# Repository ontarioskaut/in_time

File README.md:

# Hardwarové věci k etapě InTime 2025
Tento repozitář vznikl pro uchování hardwarových věcí potřebných k táborové etapě skautského oddílu Ontario - InTime 2025. Tvoří jeden celek se softwarovým řešením systému pro uchovávání časů, uživatelů a tagů, který neleznete zde: https://github.com/ontarioskaut/tabor2025. Detailnější informace jsou k mání na naši skautské wiki: https://wiki.zlin6.cz/cs/technika/intime2025.

## Obecná probematika
Pro celotáborovou hru jsme se rozhodli udělat systém, vekterém dominuje odpočítávaný čas jako měna. Členi mají RFID náramky a v dílčích částech tábora mají možnost dostat kulaté RFID tagy jakožto coiny s nějakou hodnotou. Mají jak zisky, tak výdaje za různé věci a snaží se s tím hospodařit. Aby to fungovalo, použili jsme moderní technologie a naprogramovali časový server, který řeší management uživatelů, náramků, coinů. Prostě nadstavba s API a GUI nad databází.

Tento server běží na mikropočítači (zde použit ROCK PI S s druhou WiFi kartou) a vše komunikuje bezdrátově přes WiFi. Vedoucí mají možnost zasahovat do systému skrze webové prostředí nebo webovou aplikaci používající přímo NFC API v prohlížeči, členi mohou managovat svůj čas skrze time terminals (ty umožňují platit, převádět, skenovat coiny a zjišťovat zůstatek). Terminály mají uvnitř RFID čtečku a ESP32, přes které se hardware řídí a je prováděna komunikace s časovým serverem skrze REST API. 

Další částí jsou displeje pro zobrazování aktuálních časů hráčů. K tomu jsme vybrali vyřazené Buse 210 displeje z autobusů, protože jsou velké, vypadají cool a jsou oproti LED variantám velice energeticky úsporné. Tam byl problém se zobrazováním vlastních dat, protože se pro komunikaci používá sběrnice IBIS (sériová sběrnice posazená na 24V s pomalým baudratem) s uzavřeným komunikačním protokolem. Prostě technologie někdy z 80. let. Vzhledem k tomu, že se v původních verzích panelů ani nepočítalo s vlastní grafikou, která bude často updatovaná (v panelech je databáze předpřipravených obrazovek, pomocí příkazů se přepínají). Vznikla tedy potřeba vlastního řízení. Zde nám usnadnil práci člově, který stojí za Flipity 210: https://github.com/mcer12/Flippity210. Pro naše účely stačilo naprogramovat ESP01S modulek s firmwarem, který periodicky stahuje předpřipravené obrazovky z time serveru a posílá je k zobrazení.

## displays/display_tool
- GTK aplikace sloužící k roční přípravě a testování zobrazení na Buse210 displejích. Aplikace generuje base64-encoded string, který obsahuje obrazové a adresní informace a slouží k ovládání řídící desky u displejů. 
- Existují dvě modifikace:
  - display_tool.py - tato sloužila k sériovému ovládání displejů. I2C sběrnice s displejů 
  - display_tool_web.py - modifikace, která plive data kompatibilní s webovou verzí editoru. Autorovi se totiž líp pracuje v desktopové verzi a navíc má lepší řešení low_resolution vykreslování fontů.
  
## time_terminal
- Veškeré podklady k hardwaru time_terminalu vytvořené v KiCadu. Jsou tam vytvořené přímo manifacturing data, ale ty silně nedoporučuji používat, protože design desky obsahuje mnoho chyb, které bylo potřeba manuálně předrátovat. Jedná se hlavně o špatné použití pinů, které jsou připojeny k interní flashce, takže to způsobovalo problémy u programování. Potom jsou někte použity input only piny pro output a tak dále. Bohužel si autor při kreslení schémat nedostatečně přečetl dokumentaci ESP32 modulu a pak se divil.

## firmware/esp8266_buse_cient
- Firmware pro esp01S připojené do Flipity 210 desky u displeje. Tato verze se používá ve finálním stavu systému - prostě vše se renderuje na serveru a esp jenom periodicky posílá requesty a stahuje base64-encoded obrázky, které jen vyplivne na displej.
- Pro správní fungování na největší (čelní) variantě displeje s 5 flip-dot panely byl ve Flipity210 firmwaru pozměněn limit panelů a nastavený jinší count v sekci čtení konfiguračních jumperů.
- Nevím, jak je to ve vyšší verzi Flipity210 hardwaru, ale ve verzi 2.1 je potřeba dávat pozor na voltage spiky způsobené čínským step-down modulem. Na tomto jsem při testování spálil pár STM32 procesorů. Já to řešil pomocí přidání velkého kondenzátoru a TVS na výstup. 

## firmware/ostatní
- Předchzí iterace způsobené nedostatkem espéček v mém sklepě. Jednalo se o aloučení I2C a společné řízení a potom na delší vzdálenosti použití sériového protokolu, pomocí kterého se dalo řešit posílání přímo z počítače s převodníkem.

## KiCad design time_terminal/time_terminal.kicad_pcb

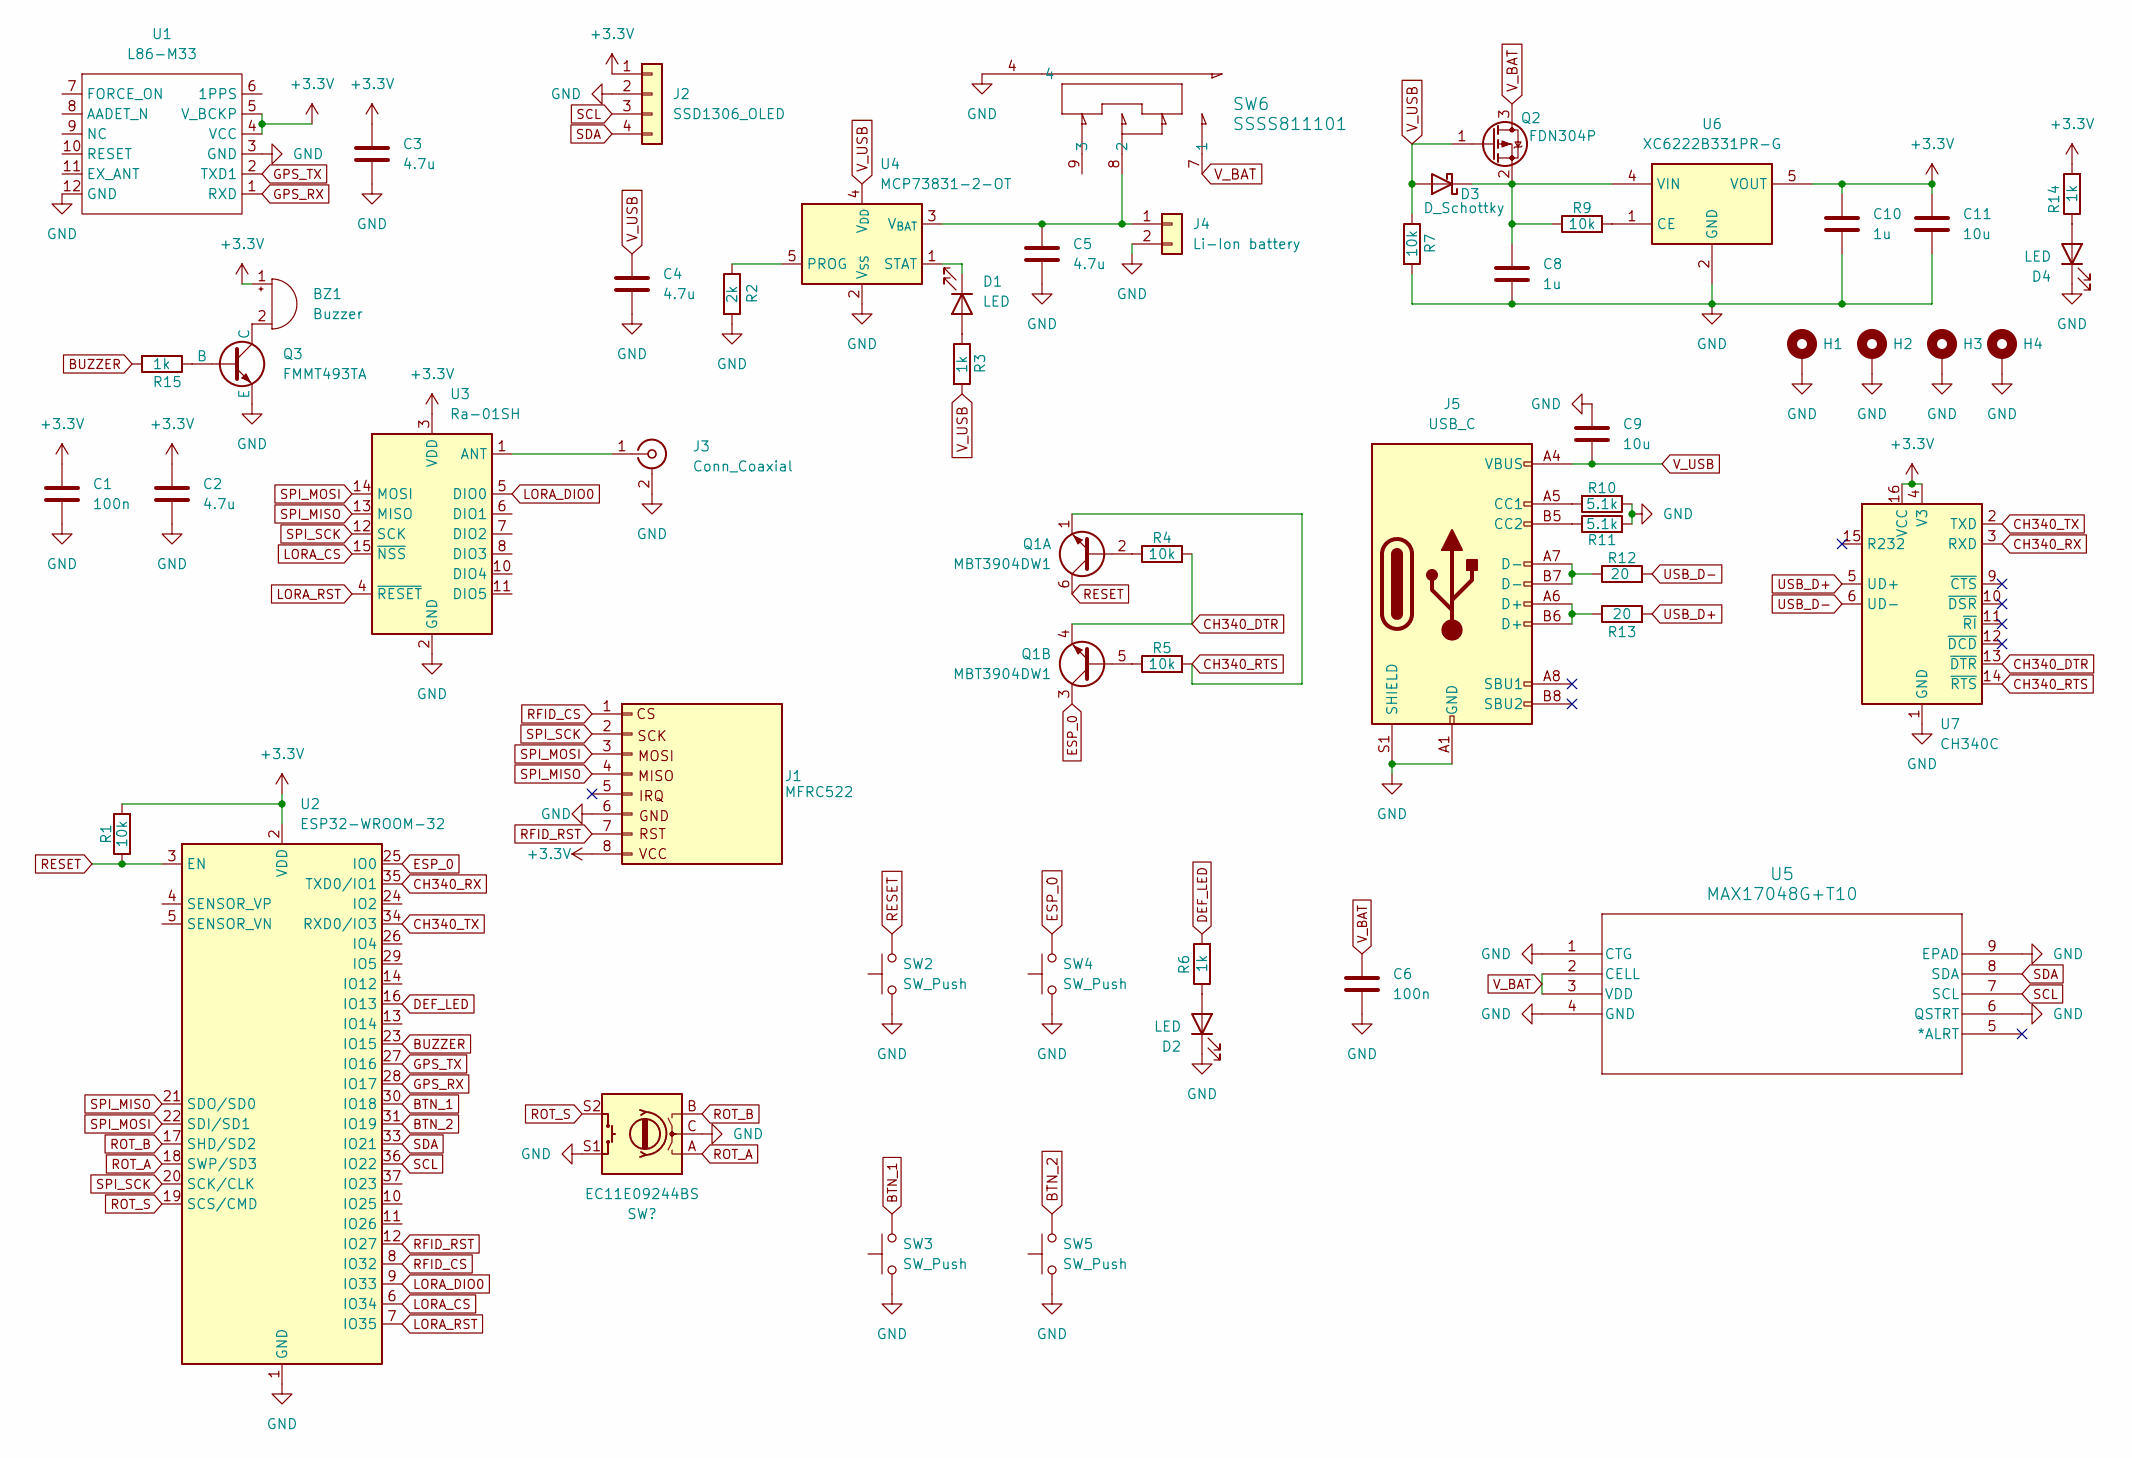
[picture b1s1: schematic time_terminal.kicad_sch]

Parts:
BZ1: Buzzer; Buzzer_TDK_PS1240P02BT_D12.2mm_H6.5mm; LCSC C360607
C1, C6: 100n; C_0603_1608Metric; LCSC C5137636
C2, C3, C4, C5: 4.7u; C_0603_1608Metric; LCSC C1705
C8, C10: 1u; C_0603_1608Metric; LCSC C1592
C9, C11: 10u; C_0603_1608Metric; LCSC C1691
D1, D2, D4: LED; LED_0603_1608Metric; LCSC C2286
D3: D_Schottky; D_SOD-123F; LCSC C223608
H1, H2, H3, H4: MountingHole_Pad; MountingHole_2.2mm_M2_Pad_Via
J1: MFRC522; PinHeader_1x08_P2.54mm_Vertical
J2: SSD1306_OLED; 128x64OLED
J3: Conn_Coaxial; SMA_Amphenol_132134-16_Vertical
J4: Li-Ion battery; BatteryHolder_Keystone_1042_1x18650
J5: USB_C; USB_C_Receptacle_HCTL_HC-TYPE-C-16P-01A; LCSC C2894897
Q1: MBT3904DW1; SOT-363_SC-70-6; LCSC C110150
Q2: FDN304P; SOT-23; LCSC C19188375
Q3: FMMT493TA; SOT-23-3; LCSC C435889
R1, R4, R5, R7, R9: 10k; R_0603_1608Metric_Pad0.98x0.95mm_HandSolder; LCSC C15401
R2: 2k; R_0603_1608Metric_Pad0.98x0.95mm_HandSolder; LCSC C25590
R3, R6, R14, R15: 1k; R_0603_1608Metric_Pad0.98x0.95mm_HandSolder; LCSC C22548
R10, R11: 5.1k; R_0603_1608Metric_Pad0.98x0.95mm_HandSolder; LCSC C2907114
R12, R13: 20; R_0603_1608Metric_Pad0.98x0.95mm_HandSolder; LCSC C25218
SW2, SW3, SW4, SW5: SW_Push; SW_Push_1P1T_XKB_TS-1187A; LCSC C318884
SW6: SSSS811101; SW4_SSSS811101_ALPS; LCSC C109335
U1: L86-M33
U2: ESP32-WROOM-32
U3: Ra-01SH; Ai-Thinker-Ra-01-LoRa
U4: MCP73831-2-OT; SOT-23-5; LCSC C424093
U5: MAX17048G+T10; 21-0168E_T822-3_MXM; LCSC C2682616
U6: XC6222B331PR-G; SOT-89-5; LCSC C3747687
U7: CH340C; SOIC-16_3.9x9.9mm_P1.27mm; LCSC C84681

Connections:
+3.3V: BZ1.1 (+), C1.1, C2.1, C3.1, C10.1, C11.1, J1.8, J2.1, R1.2, R14.2, U1.4 (VCC), U1.5 (V_BCKP), U2.2 (VDD), U3.3 (VDD), U6.5 (VOUT), U7.4 (V3), U7.16 (VCC)
BTN_1: SW3.2, U2.30 (IO18)
BTN_2: SW5.2, U2.31 (IO19)
BUZZER: R15.2, U2.23 (IO15)
CH340_DTR: Q1.4 (E2), R4.2, U7.13 (~DTR)
CH340_RTS: Q1.1 (E1), R5.2, U7.14 (~RTS)
CH340_RX: U2.35 (TXD0/IO1), U7.3 (RXD)
CH340_TX: U2.34 (RXD0/IO3), U7.2 (TXD)
DEF_LED: R6.2, U2.16 (IO13)
ESP_0: Q1.3 (C2), SW4.2, U2.25 (IO0)
GND: C1.2, C2.2, C3.2, C4.2, C5.2, C6.2, C8.2, C9.1, C10.2, C11.2, D2.1 (K), D4.1 (K), H1.1, H2.1, H3.1, H4.1, J1.6, J2.2, J3.2 (Ext), J4.2, J5.A1 (GND), J5.A12 (GND), J5.B1 (GND), J5.B12 (GND), J5.S1 (SHIELD), Q3.2 (E), R2.2, R7.2, R10.1, R11.2, SW2.1, SW3.1, SW4.1, SW5.1, SW6.4, U1.3 (GND), U1.12 (GND), U2.1 (GND), U2.15 (GND), U2.38 (GND), U2.39 (GND), U3.2 (GND), U3.9 (GND), U3.16 (GND), U4.2 (V_{SS}), U5.1 (CTG), U5.4 (GND), U5.6 (QSTRT), U5.9 (EPAD), U6.2 (GND), U7.1 (GND); also elsewhere on the board
GPS_RX: U1.1 (RXD), U2.28 (IO17)
GPS_TX: U1.2 (TXD1), U2.27 (IO16)
LORA_CS: U2.6 (IO34), U3.15 (~NSS)
LORA_DIO0: U2.9 (IO33), U3.5 (DIO0)
LORA_RST: U2.7 (IO35), U3.4 (~RESET)
unnamed: BZ1.2 (-), Q3.3 (C)
unnamed: D1.2 (A), R3.1
unnamed: D1.1 (K), U4.1 (STAT)
unnamed: D2.2 (A), R6.1
unnamed: C8.1, D3.1 (K), Q2.2 (S), R9.1, U6.4 (VIN)
unnamed: D4.2 (A), R14.1
unnamed: J3.1 (In), U3.1 (ANT)
unnamed: C5.1, J4.1, SW6.8 (2), U4.3 (V_{BAT})
unnamed: J5.A5 (CC1), R10.2
unnamed: J5.B5 (CC2), R11.1
unnamed: J5.A6 (D+), J5.B6 (D+), R13.1
unnamed: J5.A7 (D-), J5.B7 (D-), R12.1
unnamed: Q1.2 (B1), R4.1
unnamed: Q1.5 (B2), R5.1
unnamed: Q3.1 (B), R15.1
unnamed: R2.1, U4.5 (PROG)
unnamed: R9.2, U6.1 (CE)
RESET: Q1.6 (C1), R1.1, SW2.2, U2.3 (EN)
RFID_CS: J1.1, U2.8 (IO32)
RFID_RST: J1.7, U2.12 (IO27)
ROT_A: U2.18 (SWP/SD3); also elsewhere on the board
ROT_B: U2.17 (SHD/SD2); also elsewhere on the board
ROT_S: U2.19 (SCS/CMD); also elsewhere on the board
SCL: J2.3, U2.36 (IO22), U5.7 (SCL)
SDA: J2.4, U2.33 (IO21), U5.8 (SDA)
SPI_MISO: J1.4, U2.21 (SDO/SD0), U3.13 (MISO)
SPI_MOSI: J1.3, U2.22 (SDI/SD1), U3.14 (MOSI)
SPI_SCK: J1.2, U2.20 (SCK/CLK), U3.12 (SCK)
USB_D+: R13.2, U7.5 (UD+)
USB_D-: R12.2, U7.6 (UD-)
V_BAT: C6.1, Q2.3 (D), SW6.7 (1), U5.2 (CELL), U5.3 (VDD)
V_USB: C4.1, C9.2, D3.2 (A), J5.A4 (VBUS), J5.A9 (VBUS), J5.B4 (VBUS), J5.B9 (VBUS), Q2.1 (G), R3.2, R7.1, U4.4 (V_{DD})

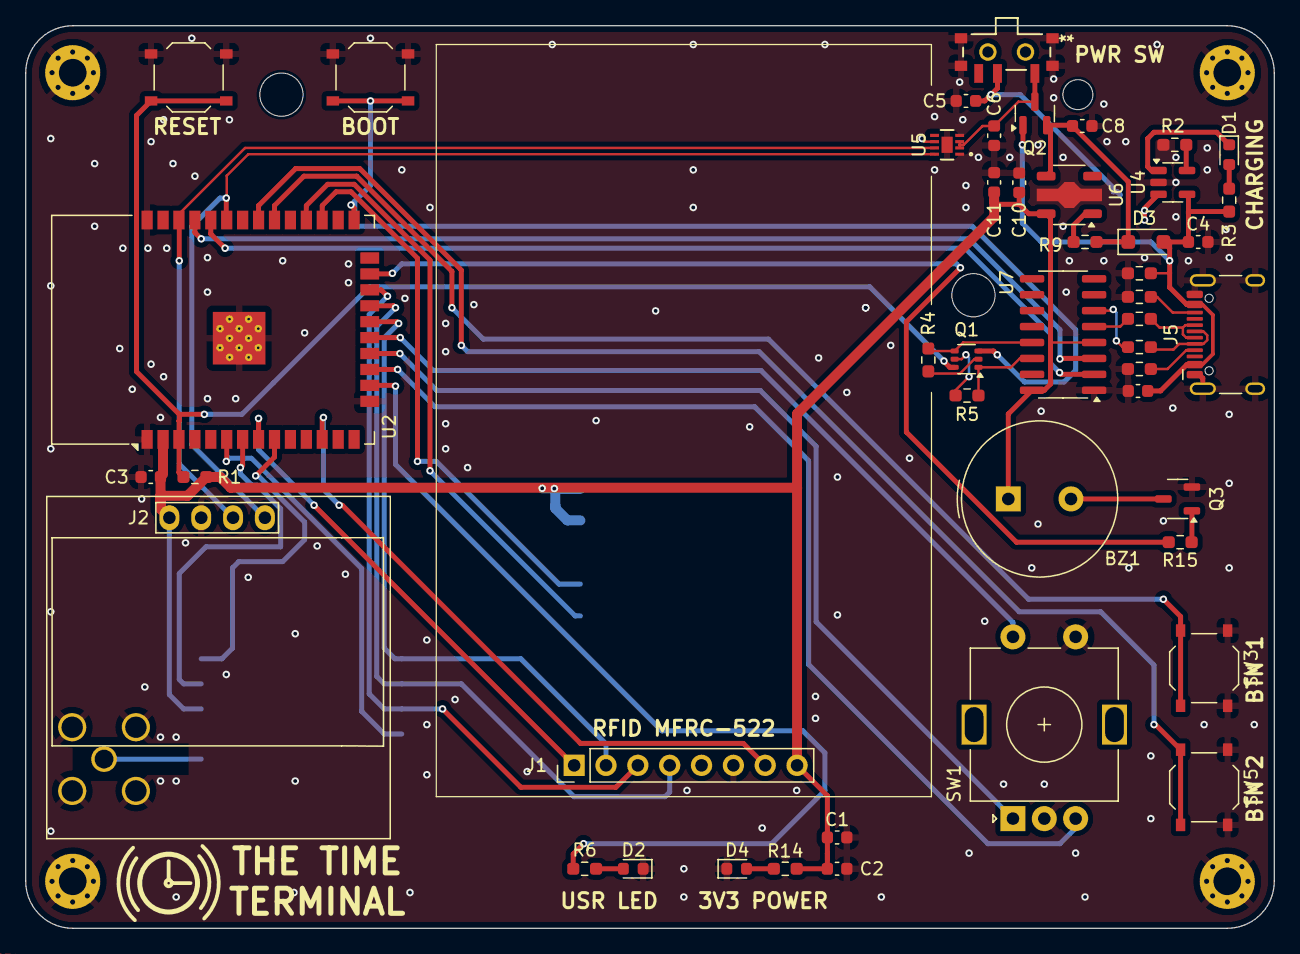
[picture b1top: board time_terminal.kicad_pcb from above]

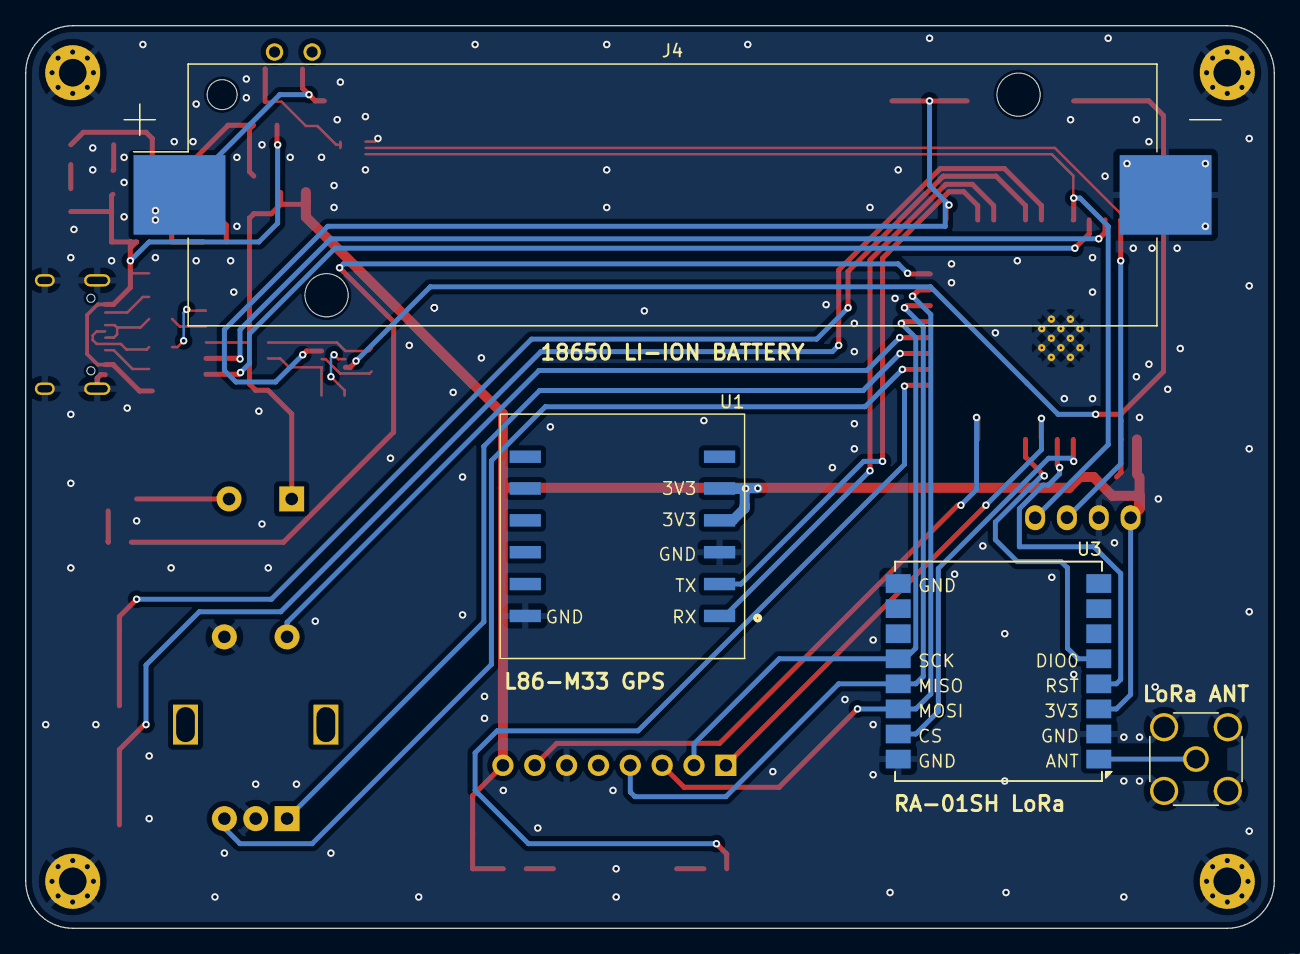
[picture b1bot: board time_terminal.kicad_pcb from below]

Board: 2 copper layers, 99.6 x 72.0 mm, 54 parts (4 on the bottom side), 48 nets.

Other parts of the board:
SW1: EC11E09244BS; RotaryEncoder_Alps_EC11E-Switch_Vertical_H20mm

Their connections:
GND: SW1.C, SW1.S1; also elsewhere on the board
ROT_A: SW1.A; also elsewhere on the board
ROT_B: SW1.B; also elsewhere on the board
ROT_S: SW1.S2; also elsewhere on the board

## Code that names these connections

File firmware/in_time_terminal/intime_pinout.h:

#ifndef intime_pinout_h
#define intime_pinout_h

// SPI
#define SCK_PIN 26
#define MISO_PIN 14
#define MOSI_PIN 12

// I2C
#define SDA_PIN 21
#define SCL_PIN 22

// I2C adresses
#define OLED_ADDR 0x3C // SSD1306
#define BAT_ADDR 0x36 // MAX17048G

// RFID (over SPI)
#define RFID_CS_PIN 32
#define RFID_RST_PIN 27

// RA-01_SH (over SPI + controll)
#define RA01_CS_PIN 34
#define RA01_RST_PIN 35
#define RA01_DIO0_PIN 33

// GPS TU10-F
#define GPS_TX 16
#define GPS_RX 17

// Rotary encoder
#define ENC_A_PIN 18
#define ENC_B_PIN 19
#define ENC_S_PIN 25

// Outputs
#define BUZZER_PIN 15
#define LED_PIN 13

#endif

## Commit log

2025-08-06 Final version of intime_terminal firmware
2025-08-25 Server config client
2025-08-30 fake intime server updates
2025-08-30 latex manual for fake_intime_server
2025-08-30 Correct pre-generated pdfs
